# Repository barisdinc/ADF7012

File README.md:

ADF7012
=======

ADF 7012 beacon projesi

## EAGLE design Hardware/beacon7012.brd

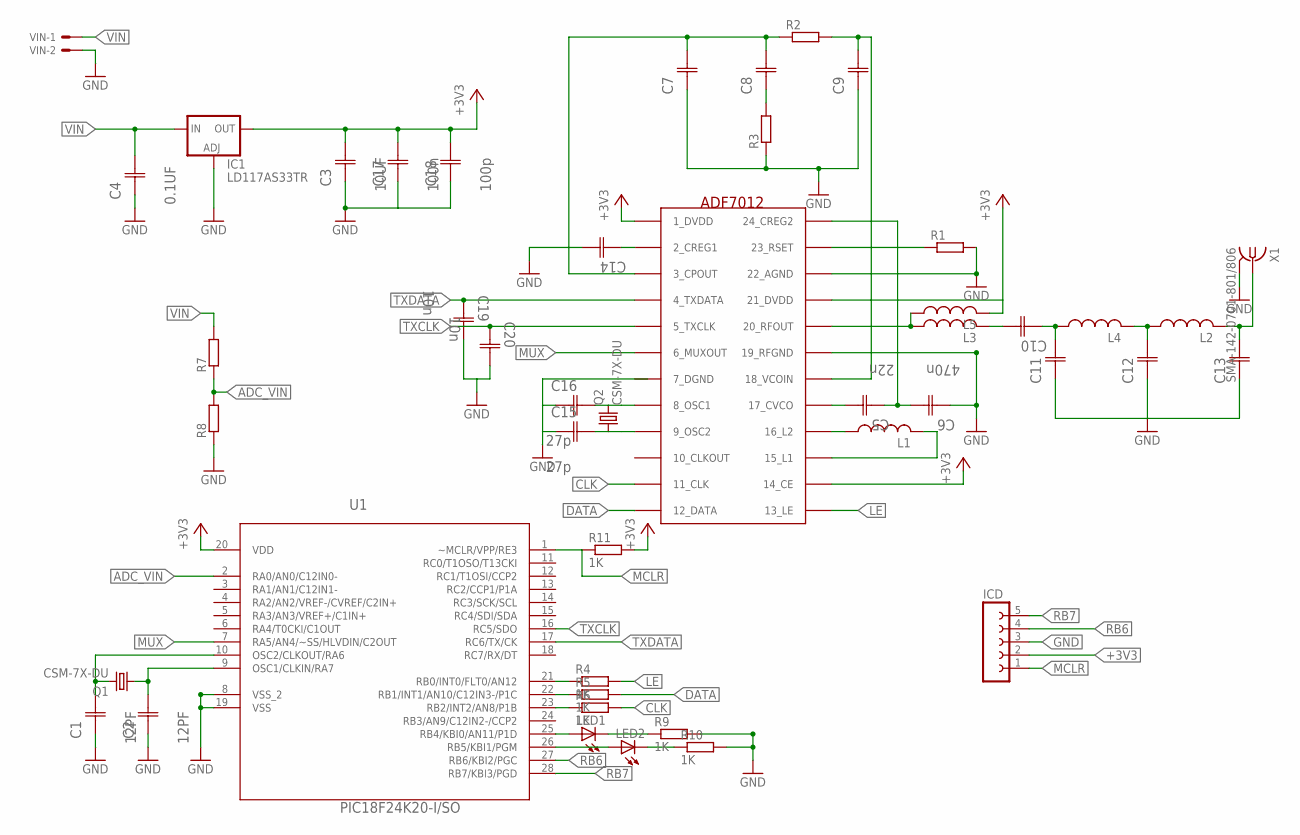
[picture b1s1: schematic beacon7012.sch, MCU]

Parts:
C1, C2: 12PF; CAPC2012X94N
C3: 10UF; CAPC2013X140N
C4: 0.1UF; CAPC2012X94N
C5: 22n; CAPC2012X94N
C6: 470n; CAPC2012X94N
C7, C8, C9, C11, C12, C13: 0805YD106MAT2A; CAPC2013X140N
C10, C14: 0805ZC104MAT2A; CAPC2012X94N
C15, C16: 27p; CAPC2012X94N
C17: 100n; CAPC2013X140N
C18: 100p; CAPC2013X140N
C19, C20: 10n; CAPC2012X94N
IC1: LD117AS33TR; SOT223
ICD: FE05-1
L1, L2, L3, L4, L5: L-USL2825P; L2825P
LED1, LED2: LEDSML0805; SML0805
Q1, Q2: CSM-7X-DU
R1, R2, R3, R7, R8: R-EU_R0805; R0805
R4, R5, R6, R9, R10, R11: 1K; R0805
U1: PIC18F24K20-I/SO; SOIC127P1030X265-28N
U$1: ADF7012
VIN: KK-156-2
X1: SMA-142-0701-801/806; J502-ND-142-0701-801/806

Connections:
+3V3: C3.2 (C2), C17.2 (C2), C18.2 (C2), IC1.4 (OUT), ICD.2, L5.2, R11.2, U1.20 (VDD), U$1.1_DVDD, U$1.14_CE, U$1.21_DVDD
ADC_VIN: R7.1, R8.2, U1.2 (RA0/AN0/C12IN0-)
CLK: R6.2, U$1.11_CLK
DATA: R5.2, U$1.12_DATA
GND: C1.1 (C1), C2.1 (C1), C3.1 (C1), C4.1 (C1), C6.1 (C1), C7.1 (C1), C9.1 (C1), C11.1 (C1), C12.1 (C1), C13.1 (C1), C14.2 (C2), C15.1 (C1), C16.1 (C1), C17.1 (C1), C18.1 (C1), C19.2 (C2), C20.2 (C2), IC1.1 (ADJ), ICD.3, R1.2, R3.1, R8.1, R9.2, R10.2, U1.8 (VSS_2), U1.19 (VSS), U$1.19_RFGND, U$1.22_AGND, VIN.2, X1.G@1 (2), X1.G@2 (2), X1.G@3 (2), X1.G@4 (2)
LE: R4.2, U$1.13_LE
MCLR: ICD.1, R11.1, U1.1 (~MCLR/VPP/RE3)
MUX: U1.7 (RA5/AN4/~SS/HLVDIN/C2OUT), U$1.6_MUXOUT
unnamed: C1.2 (C2), Q1.2, U1.10 (OSC2/CLKOUT/RA6)
unnamed: C2.2 (C2), Q1.1, U1.9 (OSC1/CLKIN/RA7)
unnamed: R5.1, U1.22 (RB1/INT1/AN10/C12IN3-/P1C)
unnamed: C16.2 (C2), Q2.2, U$1.8_OSC1
unnamed: R1.1, U$1.23_RSET
unnamed: L1.1, U$1.16_L2
unnamed: L1.2, U$1.15_L1
unnamed: C5.2 (C2), U$1.17_CVCO
unnamed: C5.1 (C1), C6.2 (C2), U$1.24_CREG2
unnamed: C7.2 (C2), C8.2 (C2), R2.1, U$1.3_CPOUT
unnamed: C9.2 (C2), R2.2, U$1.18_VCOIN
unnamed: C8.1 (C1), R3.2
unnamed: C12.2 (C2), L2.1, L4.2
unnamed: L3.1, L5.1, U$1.20_RFOUT
unnamed: C10.1 (C1), C11.2 (C2), L4.1
unnamed: C13.2 (C2), L2.2, X1.1
unnamed: C15.2 (C2), Q2.1, U$1.9_OSC2
unnamed: LED1.A, U1.25 (RB4/KBI0/AN11/P1D)
unnamed: C10.2 (C2), L3.2
unnamed: C14.1 (C1), U$1.2_CREG1
unnamed: R6.1, U1.23 (RB2/INT2/AN8/P1B)
unnamed: R4.1, U1.21 (RB0/INT0/FLT0/AN12)
unnamed: LED2.A, U1.26 (RB5/KBI1/PGM)
unnamed: LED1.C, R9.1
unnamed: LED2.C, R10.1
RB6: ICD.4, U1.27 (RB6/KBI2/PGC)
RB7: ICD.5, U1.28 (RB7/KBI3/PGD)
TXCLK: C20.1 (C1), U1.16 (RC5/SDO), U$1.5_TXCLK
TXDATA: C19.1 (C1), U1.17 (RC6/TX/CK), U$1.4_TXDATA
VIN: C4.2 (C2), IC1.3 (IN), R7.2, VIN.1

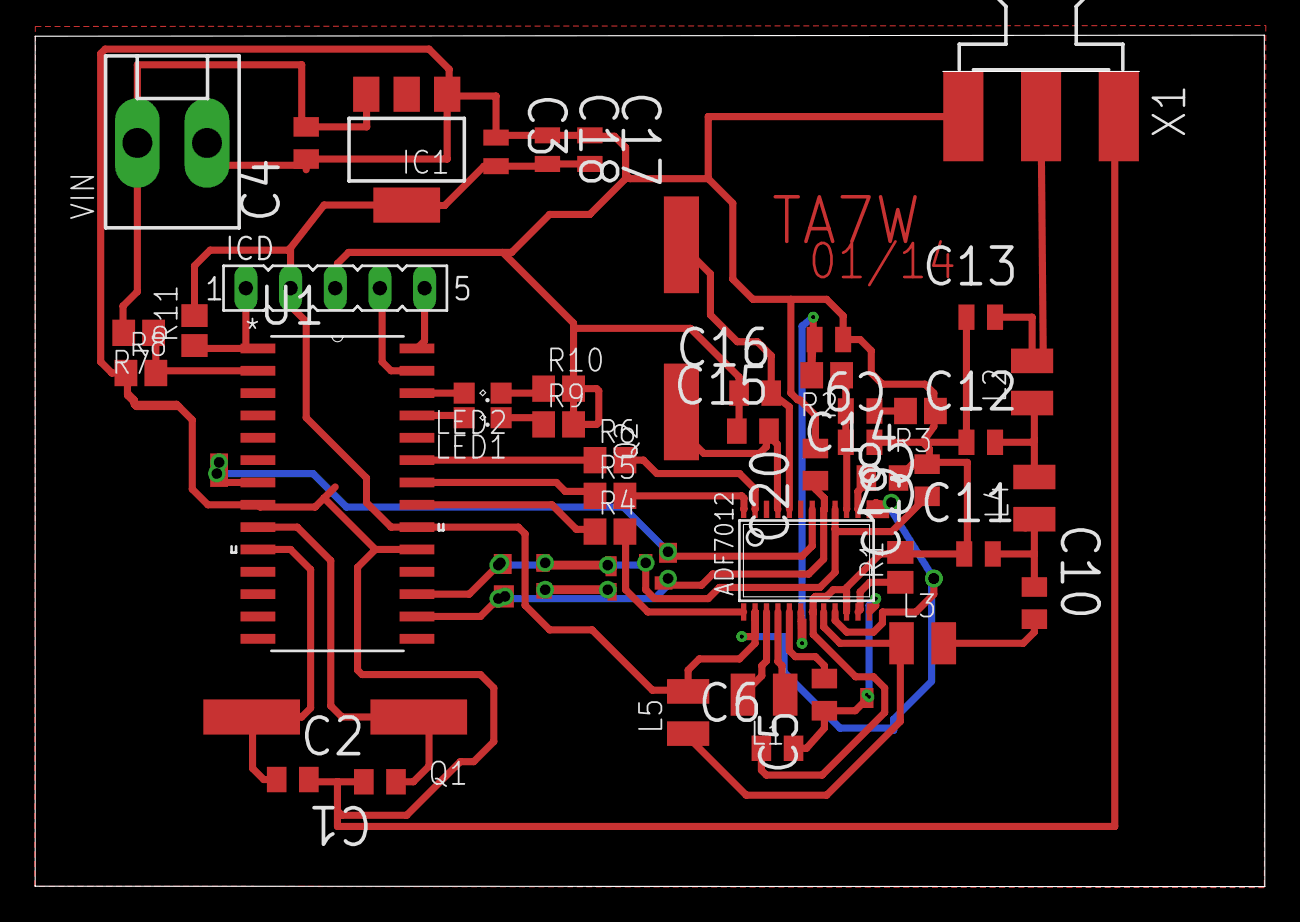
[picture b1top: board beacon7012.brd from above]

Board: 2 copper layers, 69.9 x 48.4 mm, 46 parts (0 on the bottom side), 38 nets.

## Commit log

2014-03-31 iilk versiyon
2014-03-31 ilk versiyon
2017-03-31 initial versionn
